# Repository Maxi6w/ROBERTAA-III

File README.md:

El proyecto consiste en el desarrollo de un robot móvil controlado mediante una aplicación propia, capaz de desplazarse en distintas direcciones utilizando cuatro motores que simulan patas. Además, incorporará una cámara térmica que permitirá la visualización

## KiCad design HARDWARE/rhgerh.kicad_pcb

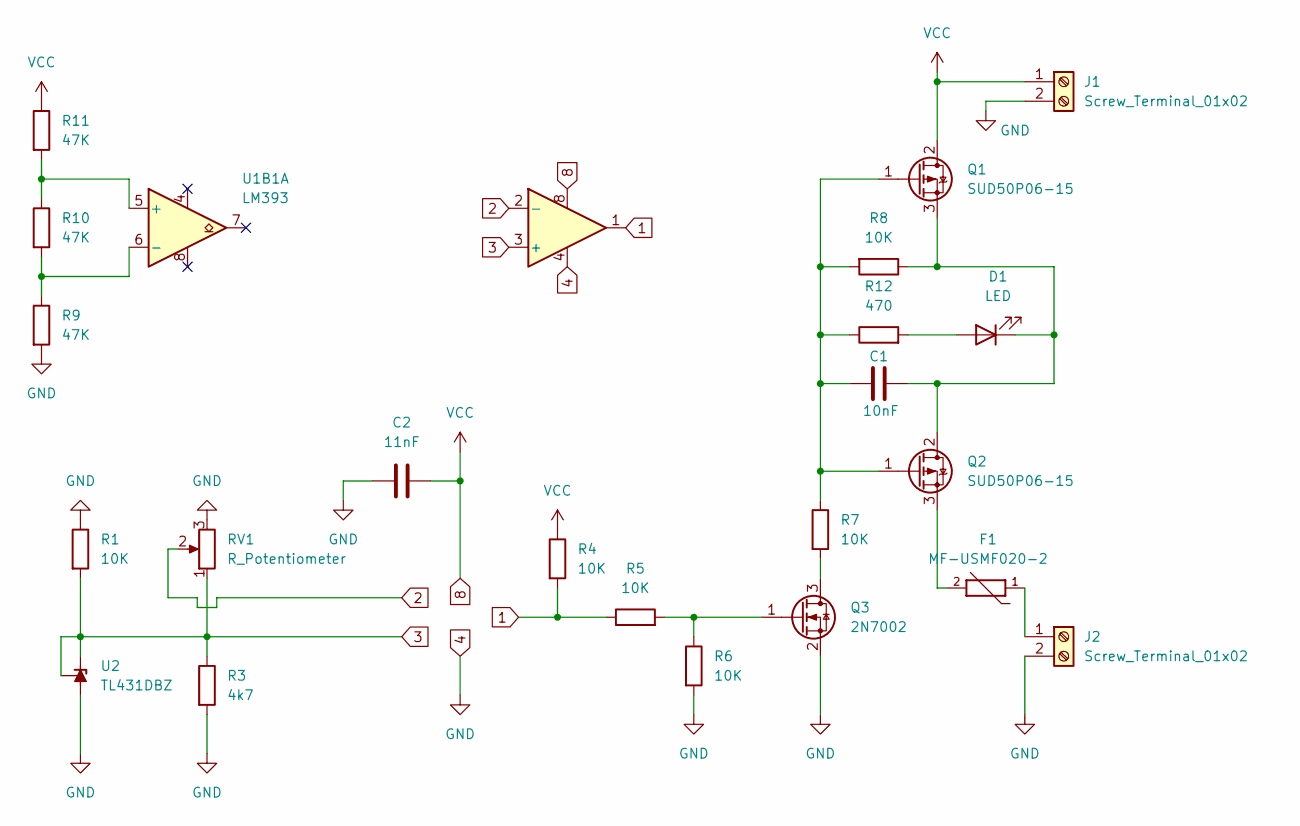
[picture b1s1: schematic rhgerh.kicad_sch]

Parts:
C1: 10nF; C_Disc_D3.0mm_W1.6mm_P2.50mm
C2: 11nF; C_Disc_D3.0mm_W1.6mm_P2.50mm
D1: LED; LED_0603_1608Metric
F1: MF-USMF020-2; FUSE_MF-USMF020-2; PARTREV S
J1, J2: Screw_Terminal_01x02; TerminalBlock_MaiXu_MX126-5.0-02P_1x02_P5.00mm
Q1, Q2: SUD50P06-15; TO-252-2
Q3: 2N7002; SOT-23
R1, R4, R5, R6, R7, R8: 10K; R_0805_2012Metric_Pad1.20x1.40mm_HandSolder
R3: 4k7; R_0805_2012Metric_Pad1.20x1.40mm_HandSolder
R9, R10, R11: 47K; R_0805_2012Metric_Pad1.20x1.40mm_HandSolder
R12: 470; R_0805_2012Metric
RV1: R_Potentiometer; TRIM_3386P-1-101TLF
U1B1: LM393; DIP794W45P254L959H508Q8
U2: TL431DBZ; SOT-23

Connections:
1: R4.2, R5.1, U1B1.1
2: RV1.2, U1B1.2 (-); also elsewhere on the board
3: R1.2, R3.1, RV1.1, U1B1.3 (+), U2.1 (K), U2.2 (REF)
4: C2.1, J1.2, J2.2, Q3.2 (S), R1.1, R3.2, R6.2, R9.2, RV1.3, U1B1.4, U2.3 (A); also elsewhere on the board
8: C2.2, J1.1, Q1.2 (D), R4.1, R11.1, U1B1.8
unnamed: D1.2 (A), R12.2
unnamed: C1.2, D1.1 (K), Q1.3 (S), Q2.2 (D), R8.1
unnamed: F1.1, J2.1
unnamed: C1.1, Q1.1 (G), Q2.1 (G), R7.1, R8.2, R12.1
unnamed: F1.2, Q2.3 (S)
unnamed: Q3.3 (D), R7.2
unnamed: Q3.1 (G), R5.2, R6.1
unnamed: R10.1, R11.2, U1B1.5 (+)
unnamed: R9.1, R10.2, U1B1.6 (-)

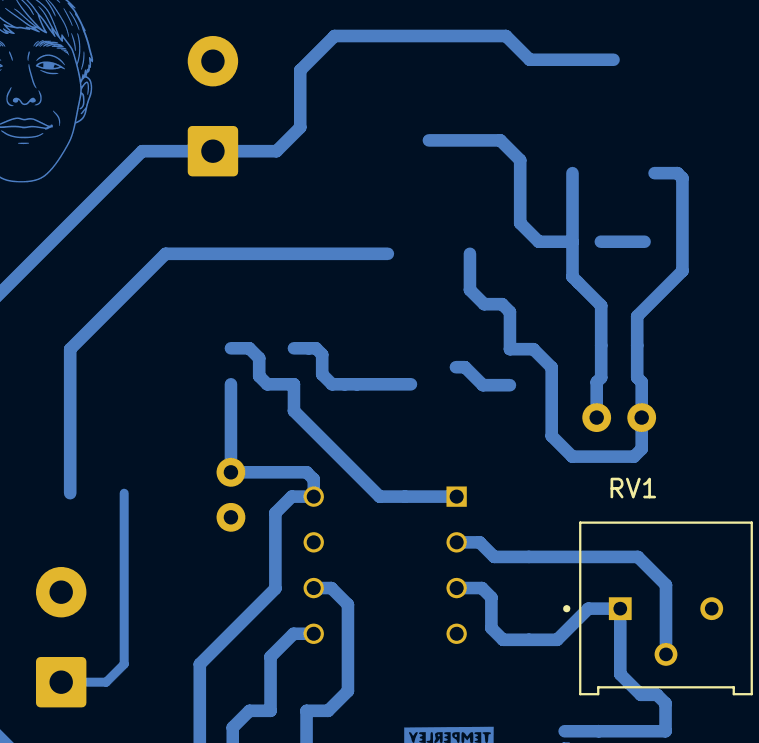
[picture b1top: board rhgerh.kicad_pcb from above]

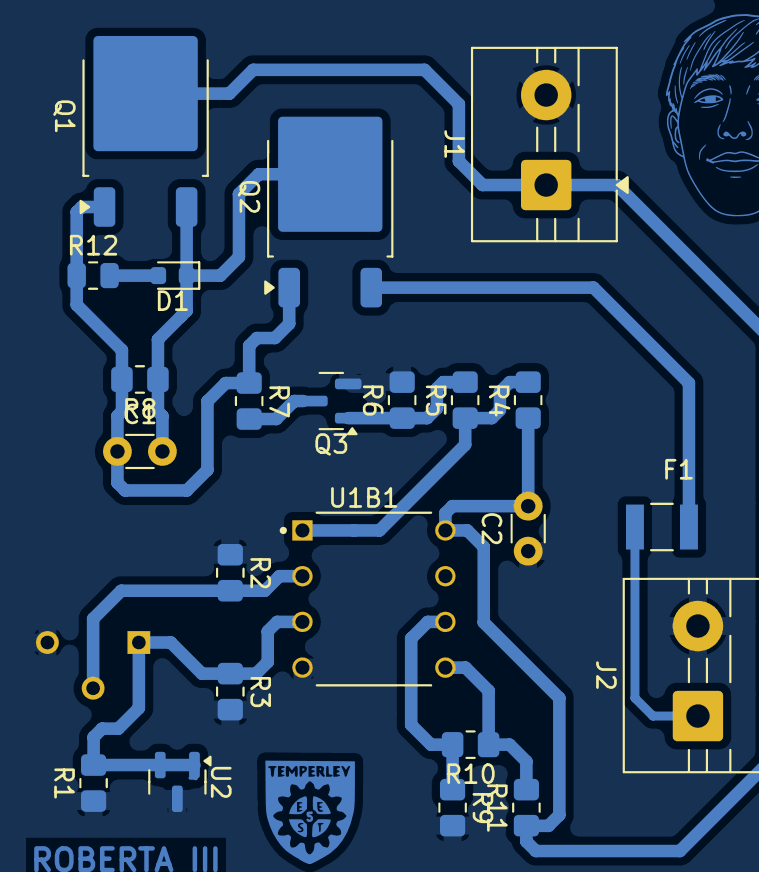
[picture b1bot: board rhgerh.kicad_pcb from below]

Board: 2 copper layers, 24 parts (23 on the bottom side), 14 nets.

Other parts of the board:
R2: 15K; R_0805_2012Metric_Pad1.20x1.40mm_HandSolder

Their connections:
2: R2.2; also elsewhere on the board
4: R2.1; also elsewhere on the board

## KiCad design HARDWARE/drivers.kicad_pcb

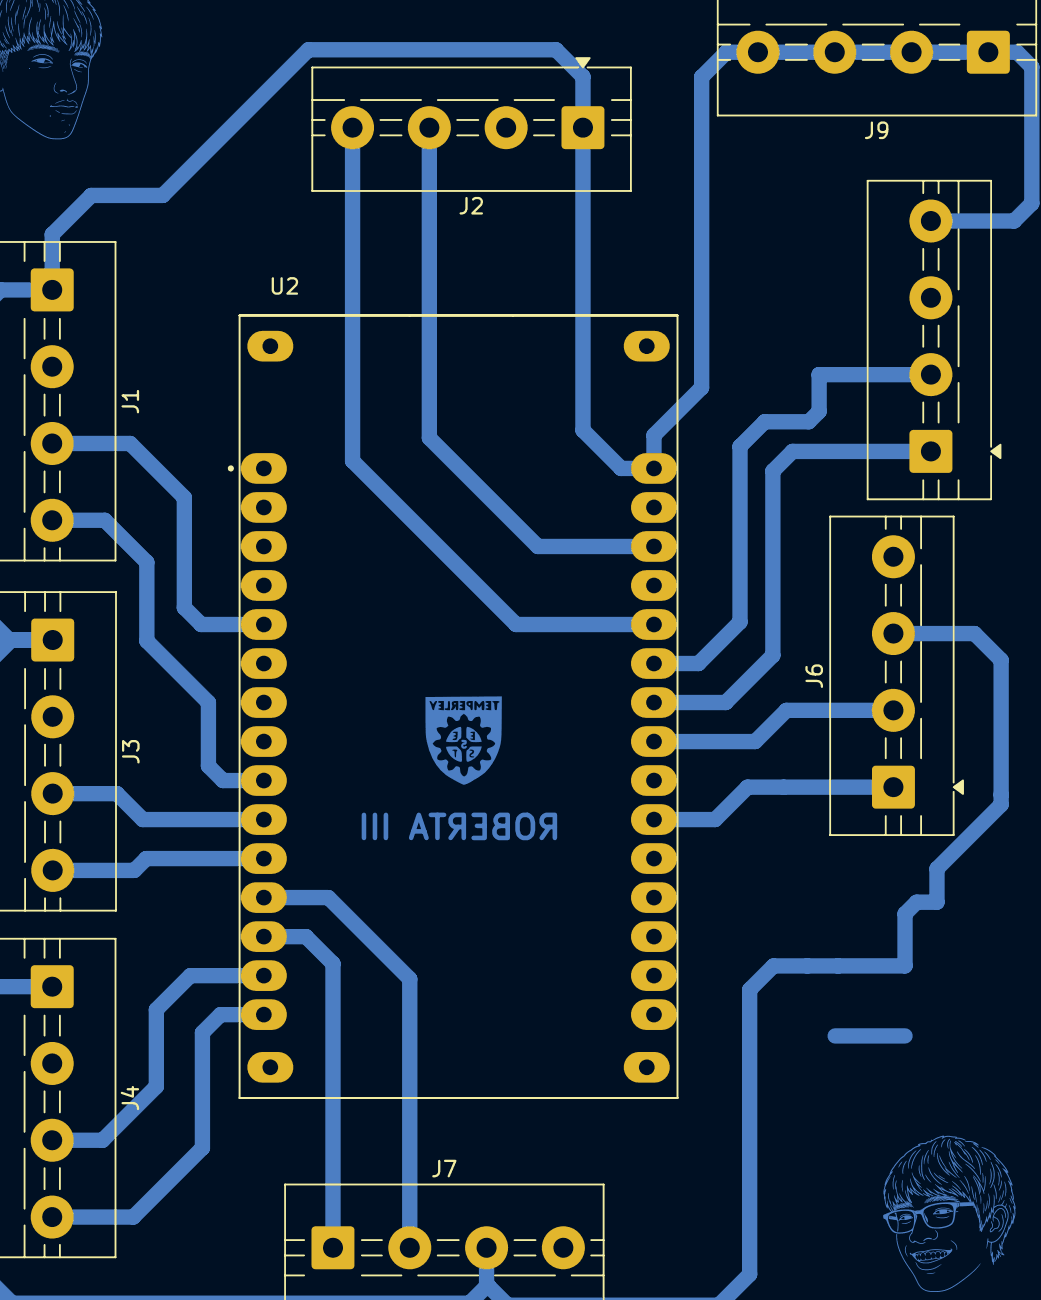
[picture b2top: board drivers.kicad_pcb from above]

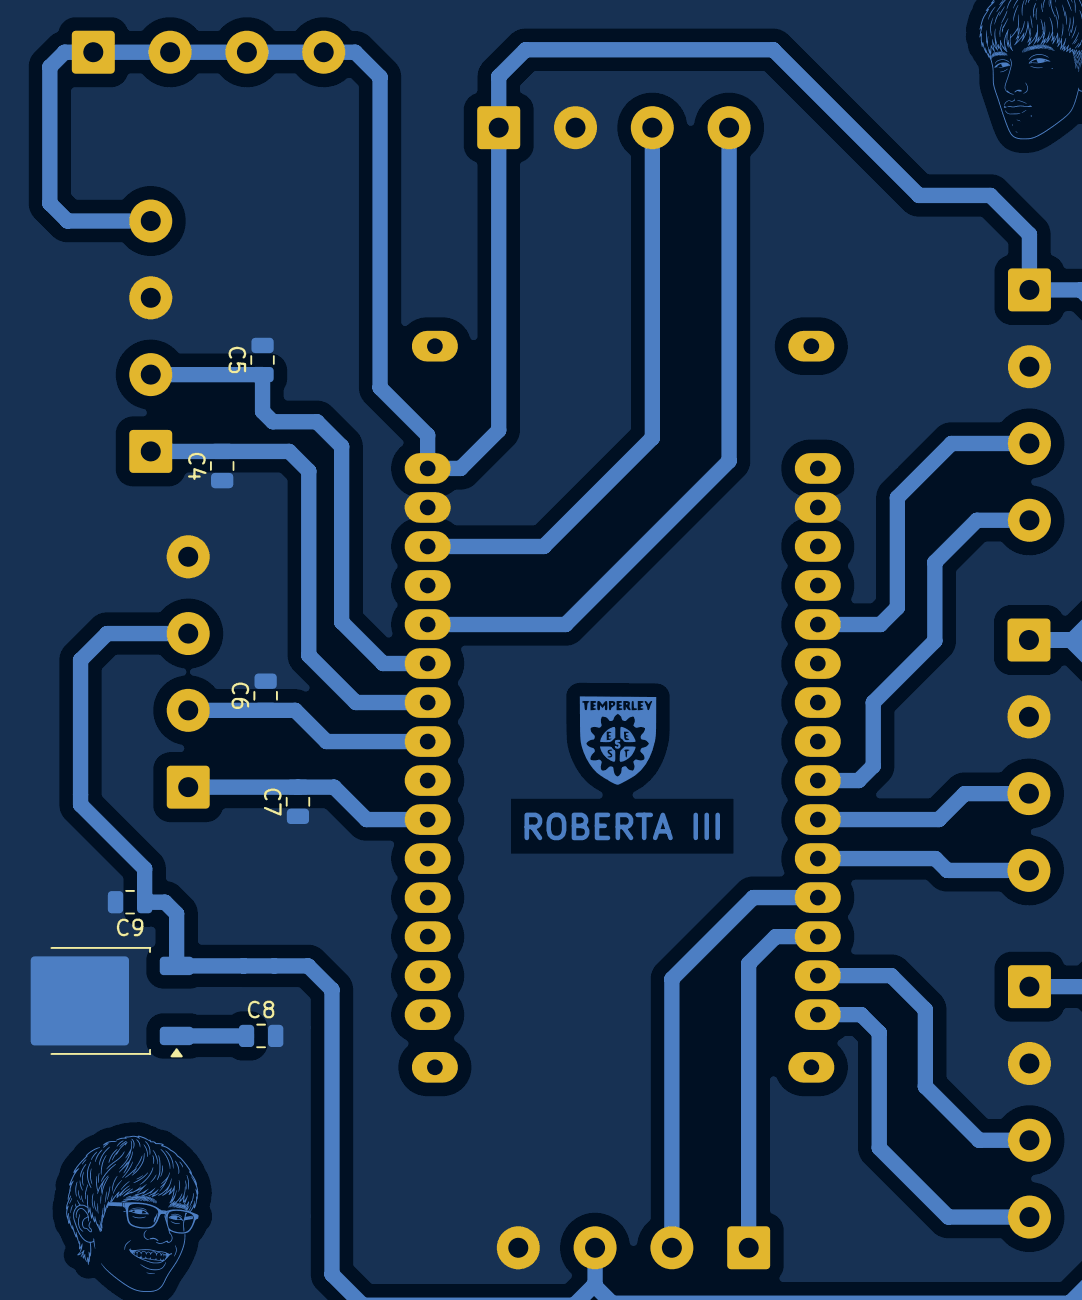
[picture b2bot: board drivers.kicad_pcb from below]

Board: 2 copper layers, 16 parts (7 on the bottom side), 17 nets.

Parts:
C4, C5, C6, C7, C8, C9: 0.1nf; C_0805_2012Metric
J1, J2, J3, J4, J5, J6: TerminalBlock_MaiXu_MX126-5.0-04P_1x04_P5.00mm
J7, J9: Screw_Terminal_01x04; TerminalBlock_MaiXu_MX126-5.0-04P_1x04_P5.00mm
U1: L7805; TO-252-2
U2: ESP32-DEVKIT-V1; MODULE_ESP32_DEVKIT_V1

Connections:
CAM_RX0: J7.2, U2.12 (RX0)
CAM_TX0: J7.1, U2.13 (TX0)
ECHO_1: C4.2, J5.1, U2.24 (D26)
ECHO_2: C7.2, J6.1, U2.21 (D32)
GND: C4.1, C5.2, C6.2, C7.1, C8.2, C9.2, J1.2, J2.2, J3.2, J4.2, J5.3, J6.4, J7.4, U1.2 (GND), U2.2 (GND), U2.29 (GND)
PWM_INPUT_1: J1.4, U2.9 (D18)
PWM_INPUT_2: J2.4, U2.26 (D14)
PWM_INPUT_3: J3.4, U2.11 (D21)
PWM_INPUT_4: J4.4, U2.15 (D23)
PWM_OUTPUT_1: J1.3, U2.5 (D4)
PWM_OUTPUT_2: J2.3, U2.28 (D13)
PWM_OUTPUT_3: J3.3, U2.10 (D19)
PWM_OUTPUT_4: J4.3, U2.14 (D22)
TRIG_1: C5.1, J5.2, U2.25 (D27)
TRIG_2: C6.1, J6.2, U2.23 (D25)
VCC: C9.1, J1.1, J2.1, J3.1, J4.1, J5.4, J6.3, J7.3, J9.1, J9.2, J9.3, J9.4, U1.3 (OUT), U2.30 (VIN)
VCC_12V: C8.1, U1.1 (IN)

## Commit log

2026-05-11 Create HARDWARE
2026-05-11 Create SOFTWARE
2026-05-11 Create 3D
